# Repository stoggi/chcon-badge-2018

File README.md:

# chcon-badge-2018
Hardware and Firmware for the ChCon 2018 badge

Made by [@jsstott](https://twitter.com/jsstott) and [@ryankurte](https://twitter.com/ryankurte)

## Assmebling your badge

See [ASSEMBLY.md](ASSEMBLY.md) for instructions, and ask in the [#badge](https://chcon-nz.slack.com/messages/CDN6BFPEV) channel in the [CHCon-NZ](https://join.slack.com/chcon-nz/shared_invite/MjA1MjM5NjY5ODQzLTE0OTg3MDAxOTEtNDUwZTMwMmEwYQ) Slack workspace for help.

## Programming your badge

You will need:

* A recent verison of the [Arduino IDE](https://www.arduino.cc/en/Main/Software) to compile and program the board
* The [Adafruit_NeoPixel](https://learn.adafruit.com/adafruit-neopixel-uberguide/arduino-library-installation) library to control the LEDs
* The [Digistump](https://digistump.com/wiki/digispark/tutorials/connecting) board library
* The EEPROM library found [here](https://github.com/digistump/DigistumpArduino/files/267174/EEPROM.zip) add under Sketch -> Include Library -> Include Zip
* A micro USB cable

To upload new firmware:

1. Open a sketch from the firmware directory.
2. From the Tools menu select Board -> Digispark (Default - 16.5Mhz)
3. From the Tools menu select Programmer -> Micronucleus.
4. Click "Upload" in the IDE. Plug in the badge, and wait 5 seconds.

> Note: Make sure your badge is powered OFF before you plug it into your computer! You can remove the battery for extra safety.

## Badge Challenge

See [CHALLENGE.md](CHALLENGE.md) to get started...

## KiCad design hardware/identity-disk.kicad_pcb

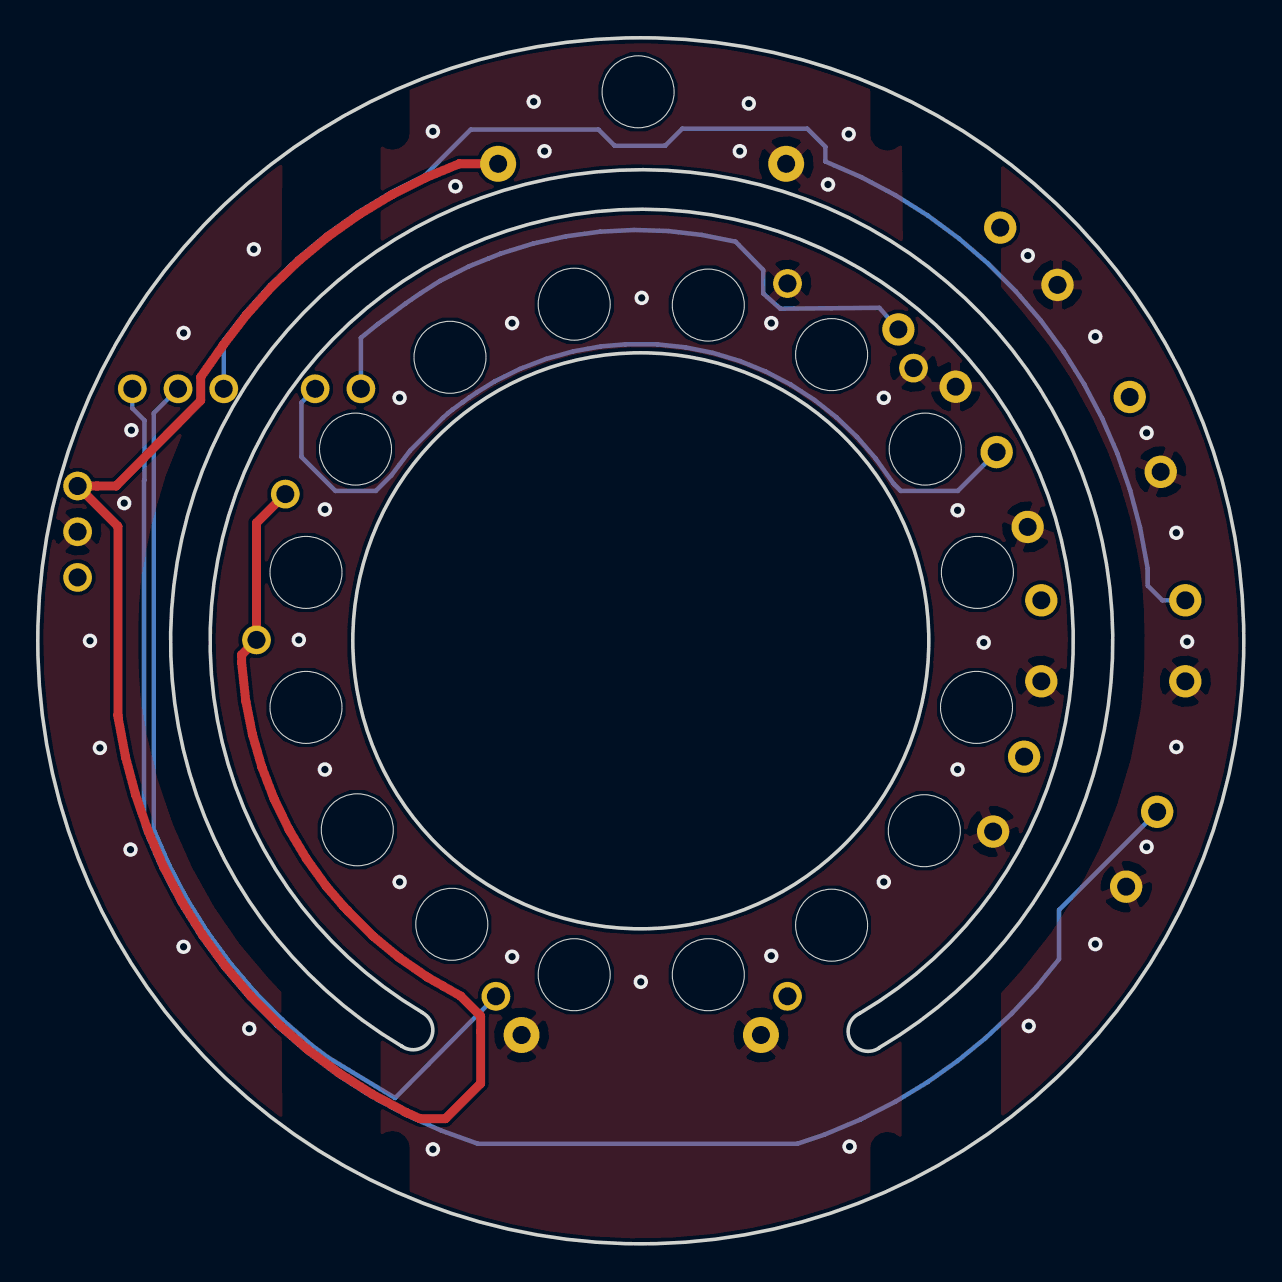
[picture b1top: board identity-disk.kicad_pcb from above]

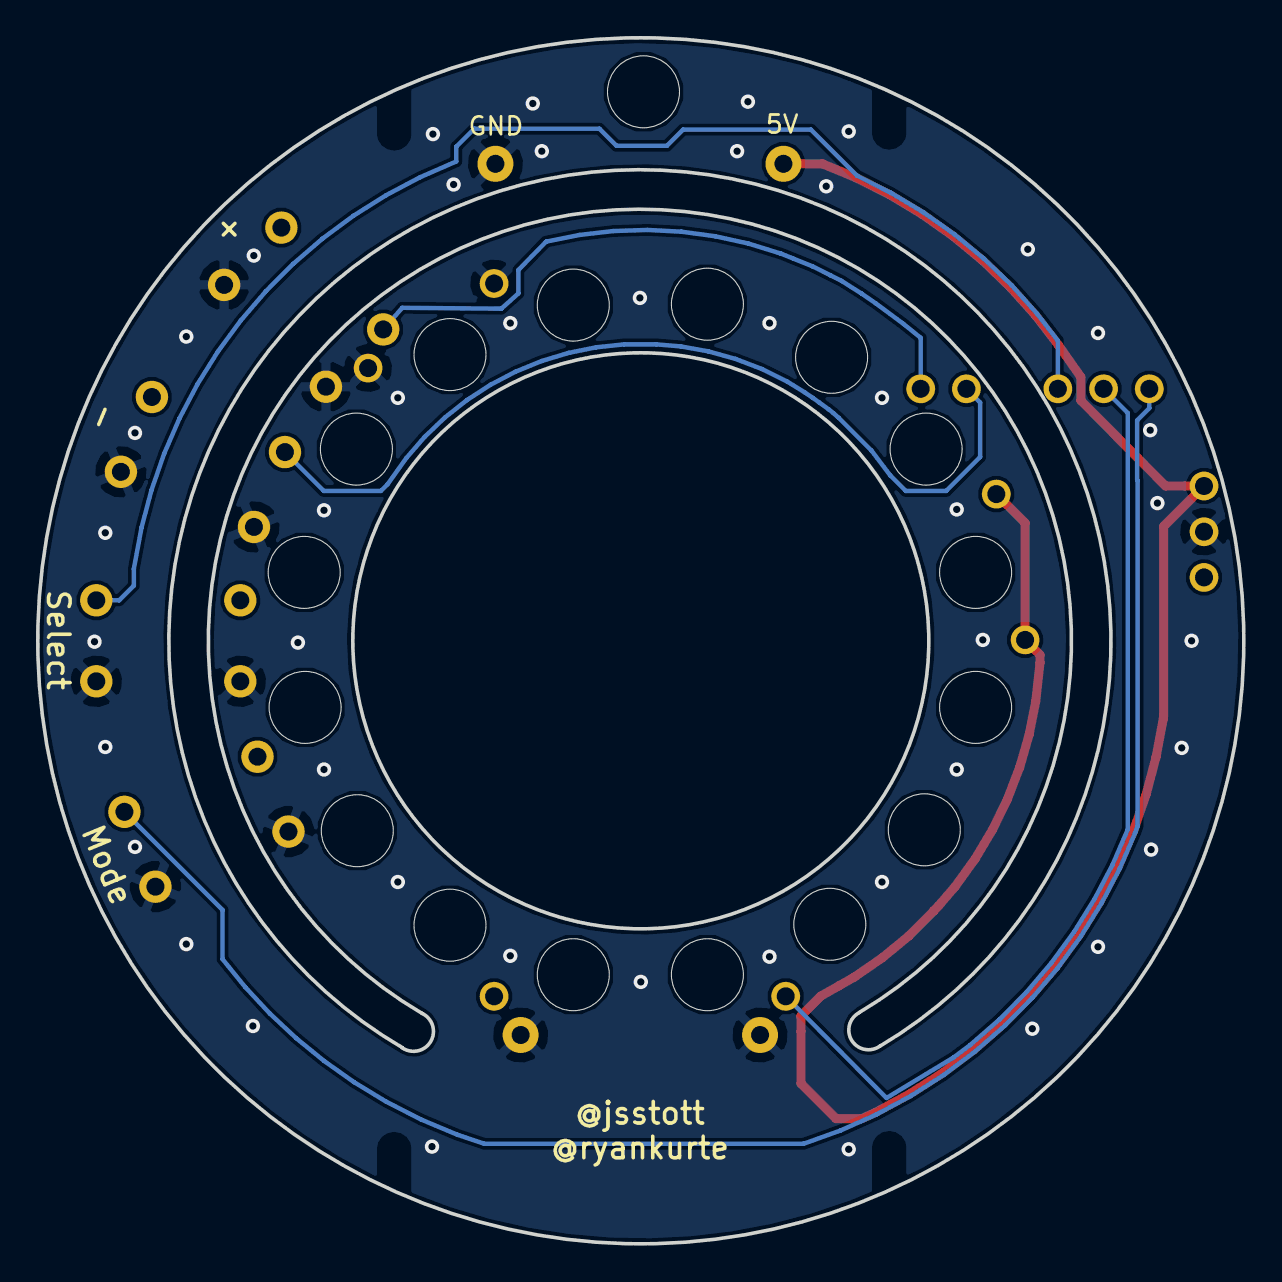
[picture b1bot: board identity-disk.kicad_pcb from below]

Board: 2 copper layers, 67.0 x 67.0 mm, 14 parts (6 on the bottom side), 7 nets.

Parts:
B1: lilypad
MH1: Lanyard Mount; lanyard_mount
MH2, MH3, MH4, MH5: Edge Cut; route_bite
MH6: Logo; logo
MH7: Front Decal; front-decal
SW1: Mode; switch
SW2: Select; switch
SW3: CCW; switch
SW4: CW; switch
U1: digispark; attiny
U2: ledring

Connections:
/5V: B1.3, U1.3, U2.1
/LED_DATA: U1.5, U2.3
/SW_Minus: SW4.1, U1.9
/SW_Mode: SW1.1, U1.4
/SW_Plus: SW3.1, U1.8
/SW_Select: SW2.1, U1.6
GND: B1.1, B1.2, B1.4, SW1.2, SW2.2, SW3.2, SW4.2, U1.2, U2.2

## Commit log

2018-10-25 Squashed ;)
2018-10-25 Updated image to clarify step2.
2018-10-26 Updated badge firmware for default color.
2018-10-26 Added README.md to badge for hex programming,
2018-10-26 Update ASSEMBLY.md
    Updated assembly docs
2018-10-26 Fixed a bug in challenge7a.hex sorry :(
2018-10-26 Added challenge8!
2018-10-26 Added a hint for challenge8
2018-10-27 Tron Lightcycle contributed by metl :D
